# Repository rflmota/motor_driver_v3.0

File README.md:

# motor_driver_v3.0
*[STM's L6470](https://www.st.com/en/motor-drivers/l6470.html)* stepper motor driver board

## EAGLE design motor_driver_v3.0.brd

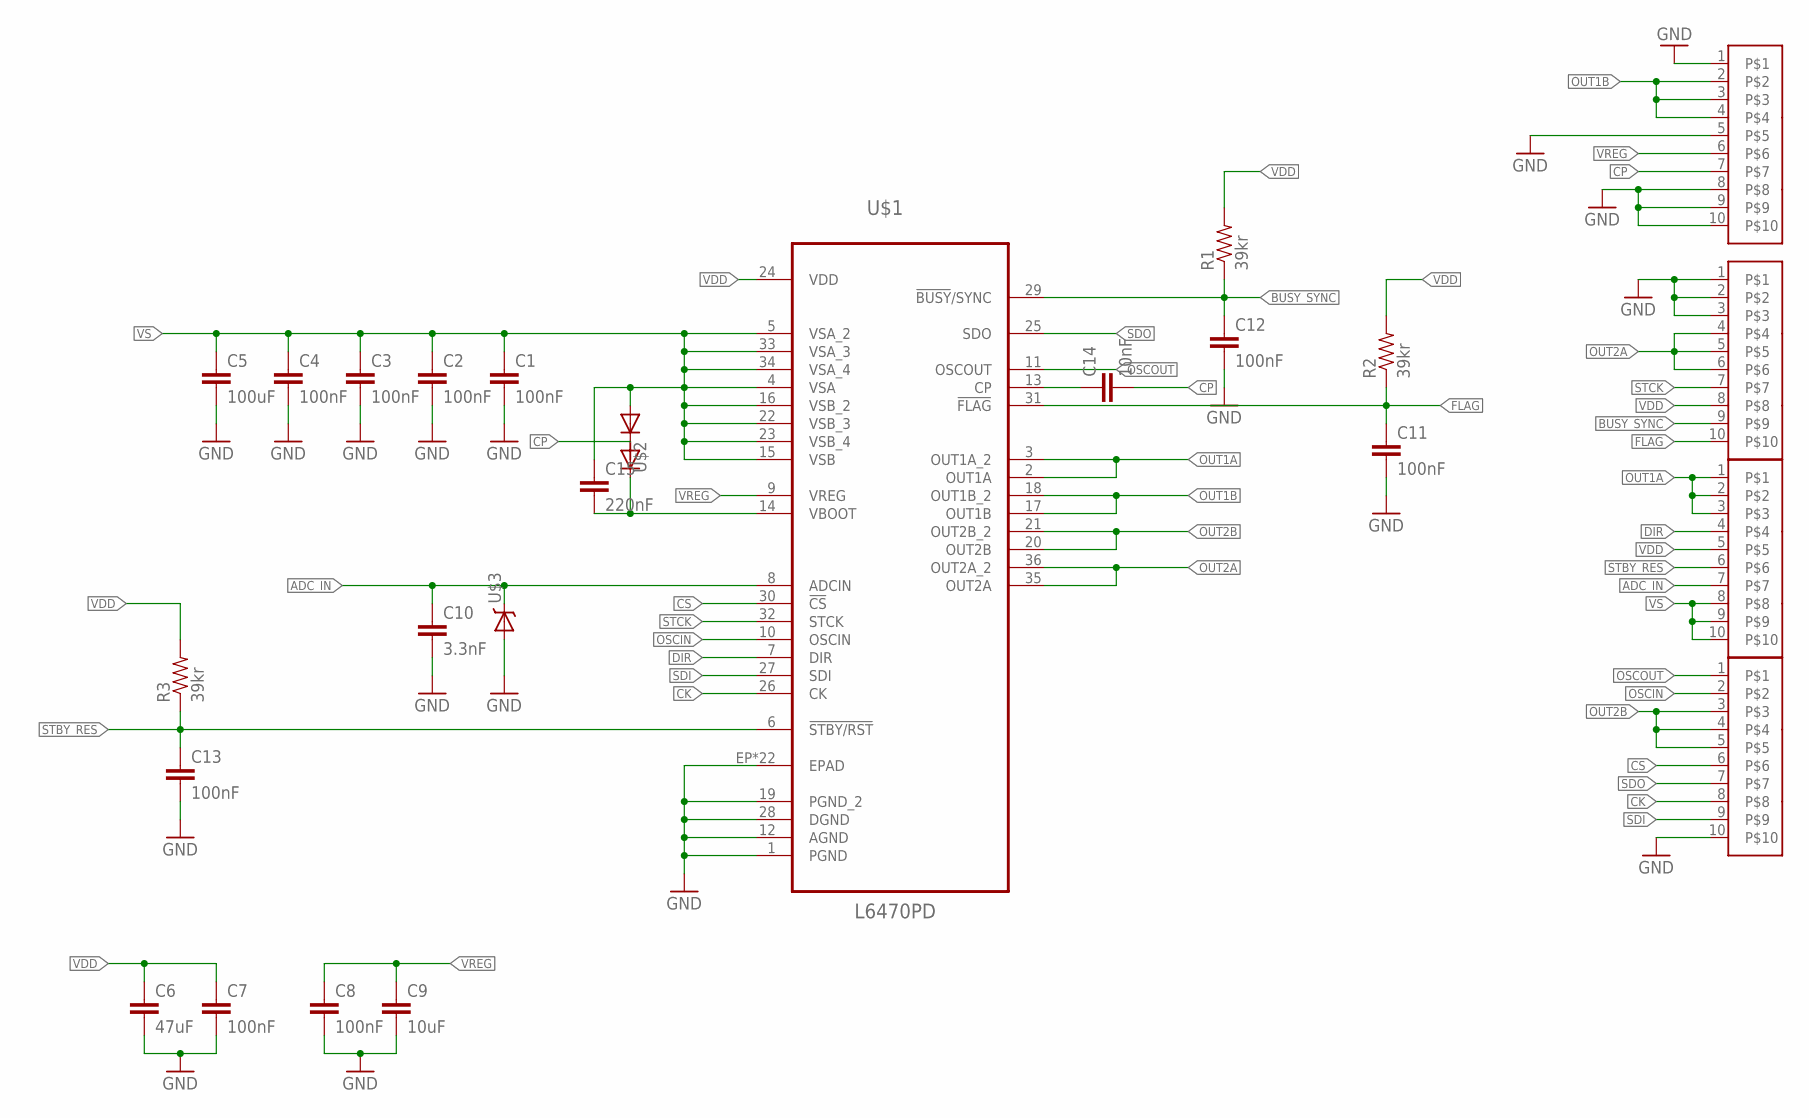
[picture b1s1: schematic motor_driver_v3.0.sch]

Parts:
C1, C2, C3, C4, C7, C8, C11, C12, C13: 100nF; 0805-CAP
C5: 100uF; CAP-10X12
C6: 47uF; 1206-CAP
C9: 10uF; 0805-CAP
C10: 3.3nF; 0805-CAP
C14: 10nF; 0805-CAP
C15: 220nF; 0805-CAP
R1, R2, R3: 39kr; 0805
U$1: L6470PD; SOP65P1400X360-37N
U$2: BAV99
U$3: BZX585
U$4, U$5, U$6, U$7: CON_TH_10PINS; CON_TH_10POS

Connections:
ADC_IN: C10.P$1 (1), U$1.8 (ADCIN), U$3.P$1 (1), U$4.7
BUSY_SYNC: C12.P$1 (1), R1.1, U$1.29 (!BUSY!/SYNC), U$5.9
CK: U$1.26 (CK), U$7.8
CP: C14.P$2 (2), U$2.P$3 (3), U$6.7
CS: U$1.30 (!CS), U$7.6
DIR: U$1.7 (DIR), U$4.4
FLAG: C11.P$1 (1), R2.1, U$1.31 (!FLAG), U$5.10
GND: C1.P$2 (2), C2.P$2 (2), C3.P$2 (2), C4.P$2 (2), C5.P$2 (2), C6.P$2 (2), C7.P$2 (2), C8.P$2 (2), C9.P$2 (2), C10.P$2 (2), C11.P$2 (2), C12.P$2 (2), C13.P$2 (2), U$1.1 (PGND), U$1.12 (AGND), U$1.19 (PGND_2), U$1.28 (DGND), U$1.EP (EPAD), U$1.VIA1 (EPAD), U$1.VIA2 (EPAD), U$1.VIA3 (EPAD), U$1.VIA4 (EPAD), U$1.VIA5 (EPAD), U$1.VIA6 (EPAD), U$1.VIA7 (EPAD), U$1.VIA8 (EPAD), U$1.VIA9 (EPAD), U$1.VIA10 (EPAD), U$1.VIA11 (EPAD), U$1.VIA12 (EPAD), U$1.VIA13 (EPAD), U$1.VIA14 (EPAD), U$1.VIA15 (EPAD), U$1.VIA16 (EPAD), U$1.VIA17 (EPAD), U$1.VIA18 (EPAD), U$1.VIA19 (EPAD), U$1.VIA20 (EPAD), U$1.VIA21 (EPAD), U$3.P$2 (2), U$5.1, U$5.2, U$5.3, U$6.1, U$6.5, U$6.8, U$6.9, U$6.10, U$7.10
unnamed: C15.P$2 (2), U$1.14 (VBOOT), U$2.P$2 (2)
unnamed: C14.P$1 (1), U$1.13 (CP)
OSCIN: U$1.10 (OSCIN), U$7.2
OSCOUT: U$1.11 (OSCOUT), U$7.1
OUT1A: U$1.2 (OUT1A), U$1.3 (OUT1A_2), U$4.1, U$4.2, U$4.3
OUT1B: U$1.17 (OUT1B), U$1.18 (OUT1B_2), U$6.2, U$6.3, U$6.4
OUT2A: U$1.35 (OUT2A), U$1.36 (OUT2A_2), U$5.4, U$5.5, U$5.6
OUT2B: U$1.20 (OUT2B), U$1.21 (OUT2B_2), U$7.3, U$7.4, U$7.5
SDI: U$1.27 (SDI), U$7.9
SDO: U$1.25 (SDO), U$7.7
STBY_RES: C13.P$1 (1), R3.1, U$1.6 (!STBY/RST), U$4.6
STCK: U$1.32 (STCK), U$5.7
VDD: C6.P$1 (1), C7.P$1 (1), R1.2, R2.2, R3.2, U$1.24 (VDD), U$4.5, U$5.8
VREG: C8.P$1 (1), C9.P$1 (1), U$1.9 (VREG), U$6.6
VS: C1.P$1 (1), C2.P$1 (1), C3.P$1 (1), C4.P$1 (1), C5.P$1 (1), C15.P$1 (1), U$1.4 (VSA), U$1.5 (VSA_2), U$1.15 (VSB), U$1.16 (VSB_2), U$1.22 (VSB_3), U$1.23 (VSB_4), U$1.33 (VSA_3), U$1.34 (VSA_4), U$2.P$1 (1), U$4.8, U$4.9, U$4.10

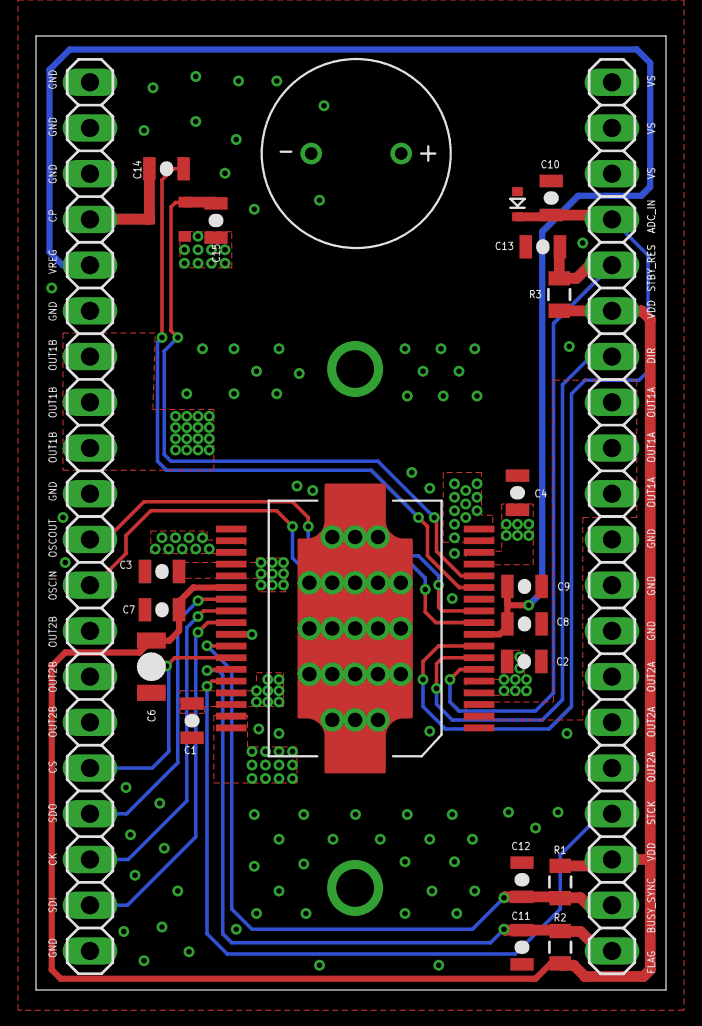
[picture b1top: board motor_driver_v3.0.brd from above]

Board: 2 copper layers, 35.0 x 53.0 mm, 25 parts (0 on the bottom side), 23 nets.

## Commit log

2019-05-23 Edited README
